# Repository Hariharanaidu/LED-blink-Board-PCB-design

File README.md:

# LED blink Board PCB design
 Designed a PCB board for blinking and controlling the intensity of  an LED using Eagle PCB design

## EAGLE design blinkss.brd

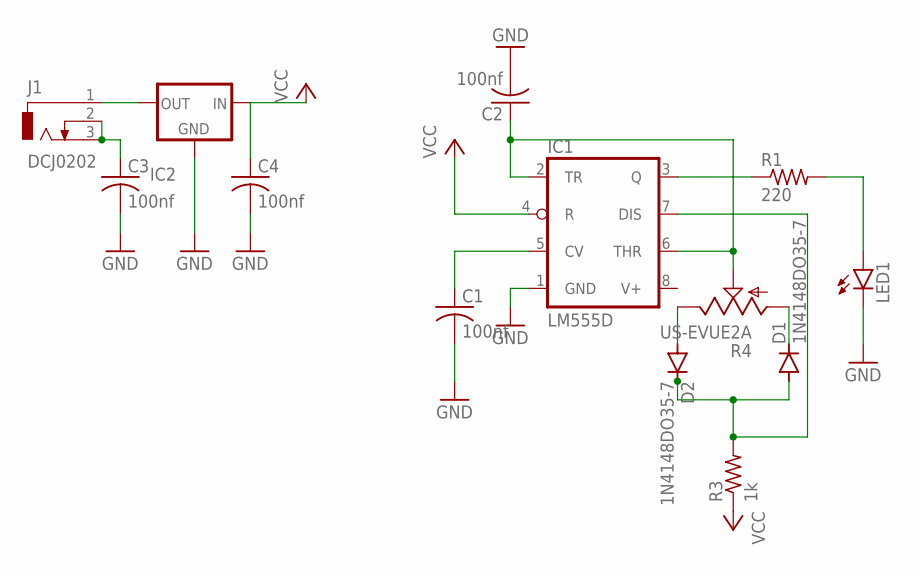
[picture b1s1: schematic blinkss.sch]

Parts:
C1, C2, C3, C4: 100nf; C0805
D1, D2: 1N4148DO35-7; DO35-7
IC1: LM555D; SO08
IC2: 79LXX
J1: DCJ0202
LED1: LED5MM
R1: 220; R0805
R3: 1k; R0805
R4: US-EVUE2A; EVUE

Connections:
GND: C1.2, C2.2, C3.2, C4.2, IC1.1 (GND), IC2.GND, LED1.K (C)
unnamed: C1.1, IC1.5 (CV)
unnamed: IC1.3 (Q), R1.1
unnamed: LED1.A, R1.2
unnamed: D1.C, R4.1 (A)
unnamed: D2.A, R4.3 (E)
unnamed: IC2.OUT, J1.1
unnamed: C2.1, IC1.2 (TR), IC1.6 (THR), R4.2 (S)
unnamed: C3.1, J1.2, J1.3
unnamed: D1.A, D2.C, IC1.7 (DIS), IC1.8 (V+), R3.2
VCC: C4.1, IC1.4 (R), IC2.IN, R3.1

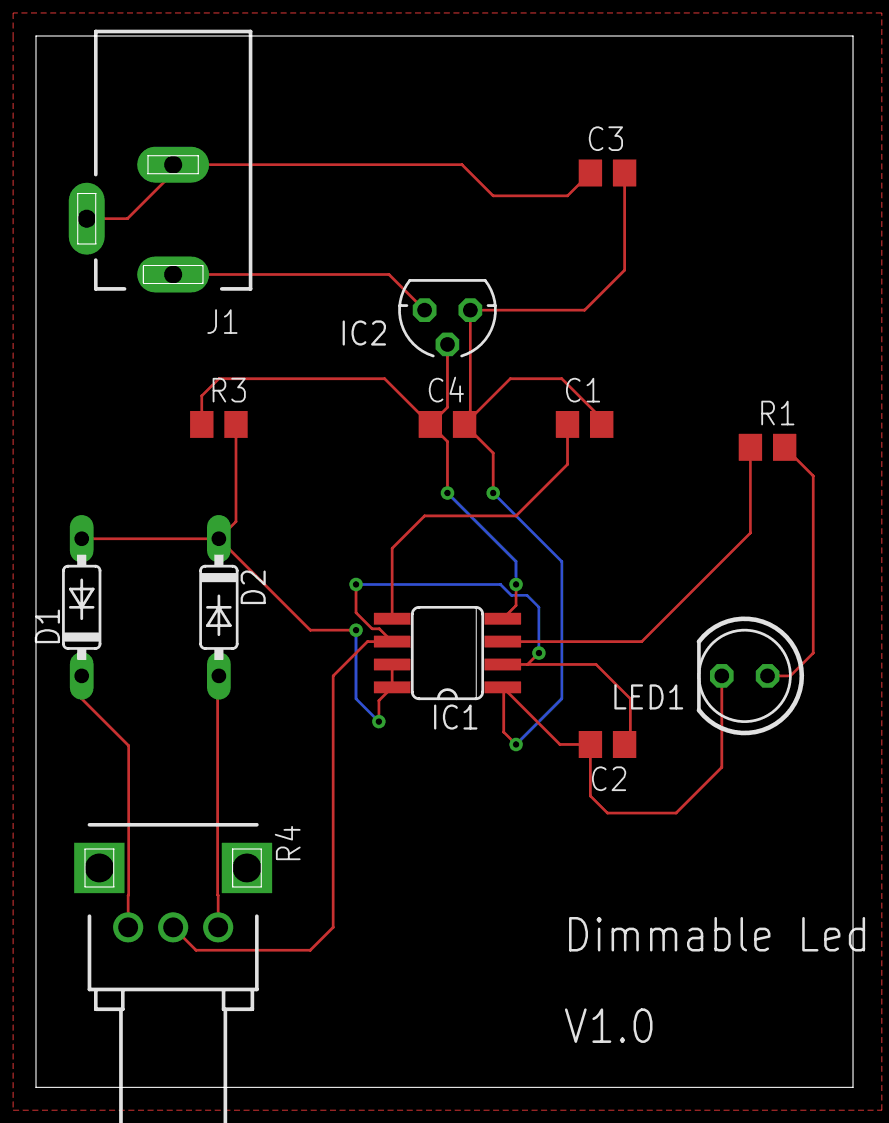
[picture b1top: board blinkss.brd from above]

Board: 2 copper layers, 45.4 x 58.4 mm, 13 parts (0 on the bottom side), 11 nets.

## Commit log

2023-11-16 files upload
